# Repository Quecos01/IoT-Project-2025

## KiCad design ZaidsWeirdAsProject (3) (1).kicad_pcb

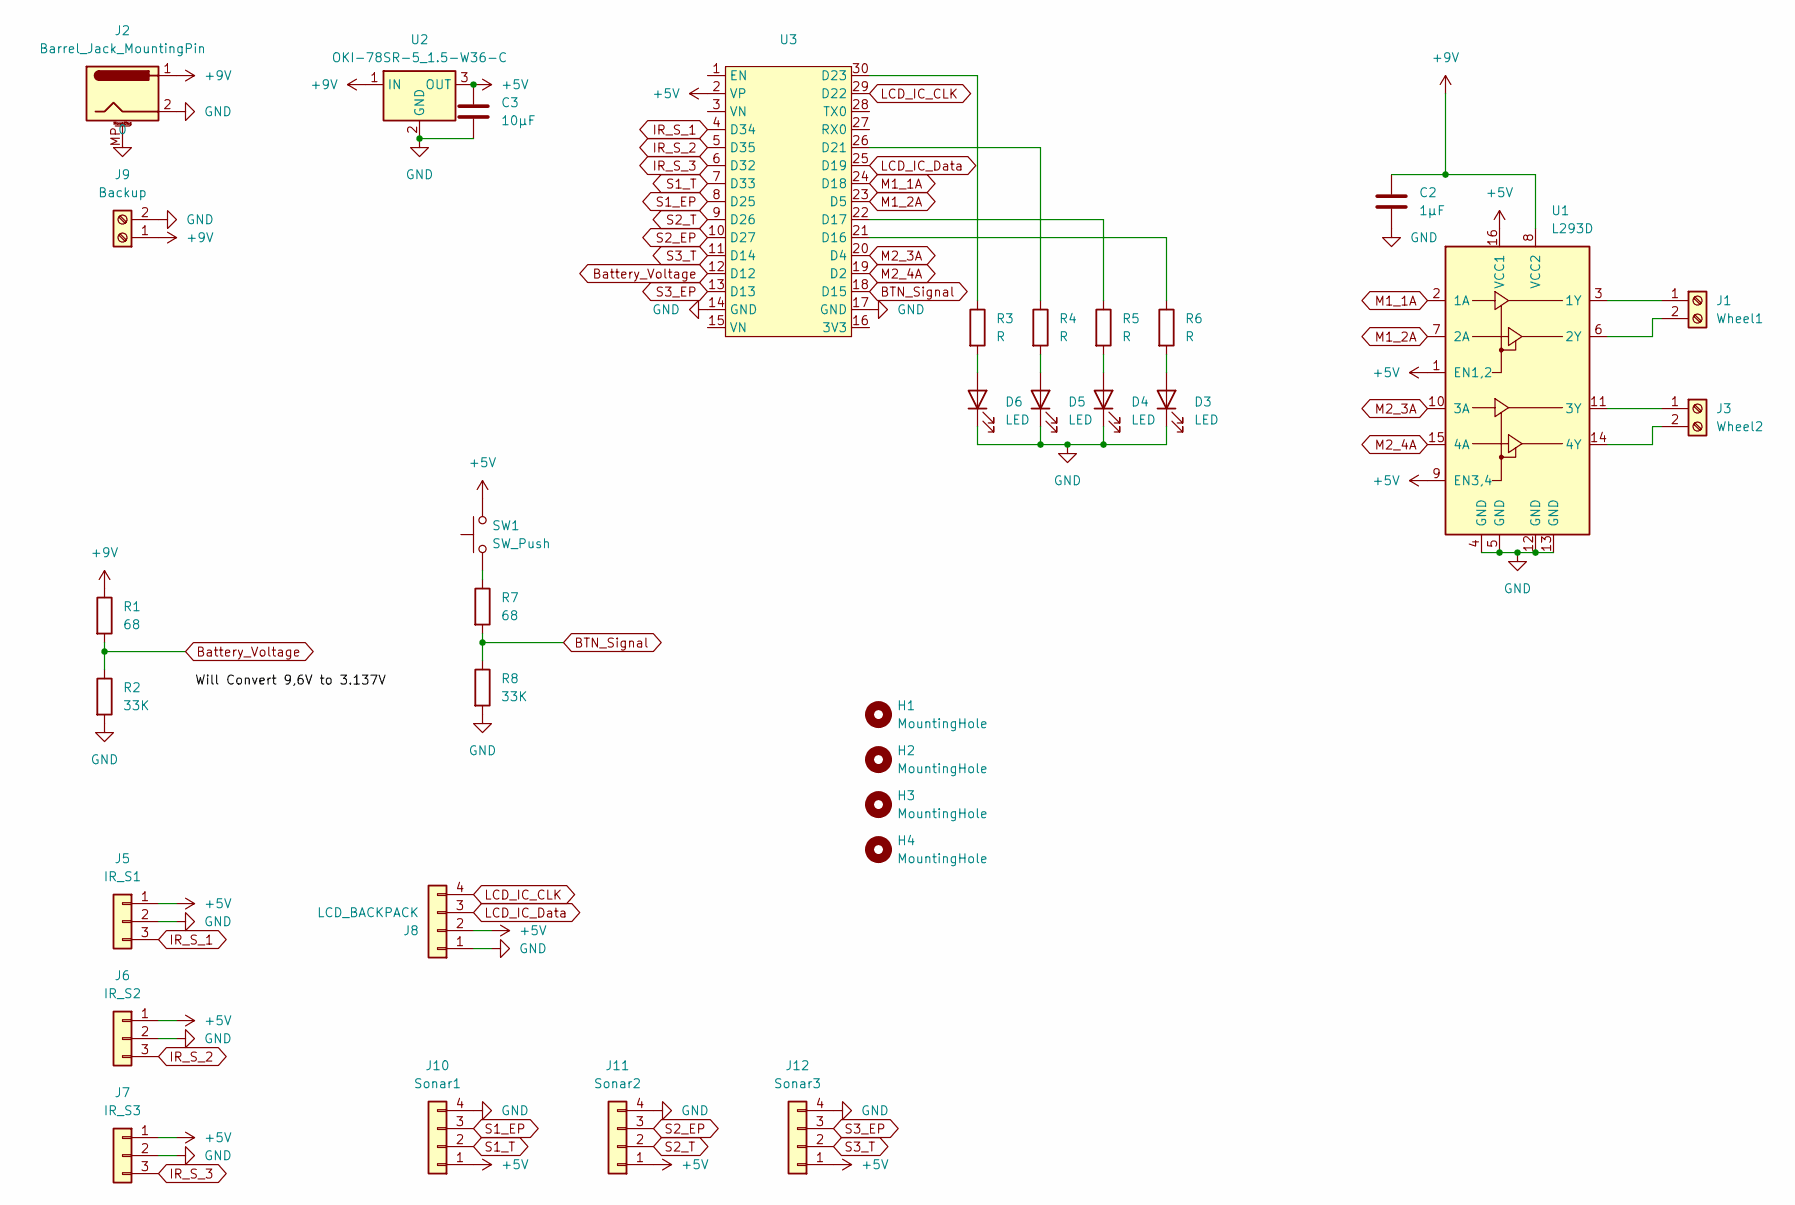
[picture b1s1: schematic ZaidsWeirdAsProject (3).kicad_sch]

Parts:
C2: 1µF; C_Disc_D3.0mm_W1.6mm_P2.50mm
C3: 10µF; C_Disc_D3.0mm_W1.6mm_P2.50mm
D3, D4, D5, D6: LED; LED_D3.0mm
H1, H2, H3, H4: MountingHole; MountingHole_3.2mm_M3
J1: Wheel1; TerminalBlock_Phoenix_MKDS-1,5-2-5.08_1x02_P5.08mm_Horizont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
J2: Barrel_Jack_MountingPin; BarrelJack_CUI_PJ-063AH_Horizontal
J3: Wheel2; TerminalBlock_Phoenix_MKDS-1,5-2-5.08_1x02_P5.08mm_Horizont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
J5: IR_S1; PinHeader_1x03_P2.54mm_Vertical
J6: IR_S2; PinHeader_1x03_P2.54mm_Vertical
J7: IR_S3; PinHeader_1x03_P2.54mm_Vertical
J8: LCD_BACKPACK; PinHeader_1x04_P2.54mm_Vertical
J9: Backup; TerminalBlock_Phoenix_MKDS-1,5-2-5.08_1x02_P5.08mm_Horizont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
J10: Sonar1; PinHeader_1x04_P2.54mm_Vertical
J11: Sonar2; PinHeader_1x04_P2.54mm_Vertical
J12: Sonar3; PinHeader_1x04_P2.54mm_Vertical
R1, R7: 68; R_Axial_DIN0204_L3.6mm_D1.6mm_P7.62mm_Horizontal
R2, R8: 33K; R_Axial_DIN0204_L3.6mm_D1.6mm_P7.62mm_Horizontal
R3, R4, R5, R6: R; R_Axial_DIN0204_L3.6mm_D1.6mm_P7.62mm_Horizontal
SW1: SW_Push; SW_PUSH-12mm
U1: L293D; DIP-16_W7.62mm
U2: OKI-78SR-5_1.5-W36-C; Converter_DCDC_Murata_OKI-78SR_Vertical
U3: ZaidESP32-C3-DevKitM-1

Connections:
0: J2.MP (MountPin)
+5V: C3.1, J5.1, J6.1, J7.1, J8.2, J10.1, J11.1, J12.1, SW1.2, U1.1 (EN1,2), U1.9 (EN3,4), U1.16 (VCC1), U2.3 (OUT), U3.2 (VP)
+9V: C2.1, J2.1, J9.1, R1.1, U1.8 (VCC2), U2.1 (IN)
BTN_Signal: R7.2, R8.1, U3.18 (D15)
Battery_Voltage: R1.2, R2.1, U3.12 (D12)
GND: C2.2, C3.2, D3.1 (K), D4.1 (K), D5.1 (K), D6.1 (K), J2.2, J5.2, J6.2, J7.2, J8.1, J9.2, J10.4, J11.4, J12.4, R2.2, R8.2, U1.4 (GND), U1.5 (GND), U1.12 (GND), U1.13 (GND), U2.2 (GND), U3.14 (GND), U3.17 (GND)
IR_S_1: J5.3, U3.4 (D34)
IR_S_2: J6.3, U3.5 (D35)
IR_S_3: J7.3, U3.6 (D32)
LCD_IC_CLK: J8.4, U3.29 (D22)
LCD_IC_Data: J8.3, U3.25 (D19)
M1_1A: U1.2 (1A), U3.24 (D18)
M1_2A: U1.7 (2A), U3.23 (D5)
M2_3A: U1.10 (3A), U3.20 (D4)
M2_4A: U1.15 (4A), U3.19 (D2)
unnamed: D3.2 (A), R6.2
unnamed: D4.2 (A), R5.2
unnamed: D5.2 (A), R4.2
unnamed: D6.2 (A), R3.2
unnamed: J1.1, U1.3 (1Y)
unnamed: J1.2, U1.6 (2Y)
unnamed: J3.1, U1.11 (3Y)
unnamed: J3.2, U1.14 (4Y)
unnamed: R7.1, SW1.1
unnamed: R6.1, U3.21 (D16)
unnamed: R5.1, U3.22 (D17)
unnamed: R4.1, U3.26 (D21)
unnamed: R3.1, U3.30 (D23)
S1_EP: J10.3, U3.8 (D25)
S1_T: J10.2, U3.7 (D33)
S2_EP: J11.3, U3.10 (D27)
S2_T: J11.2, U3.9 (D26)
S3_EP: J12.3, U3.13 (D13)
S3_T: J12.2, U3.11 (D14)

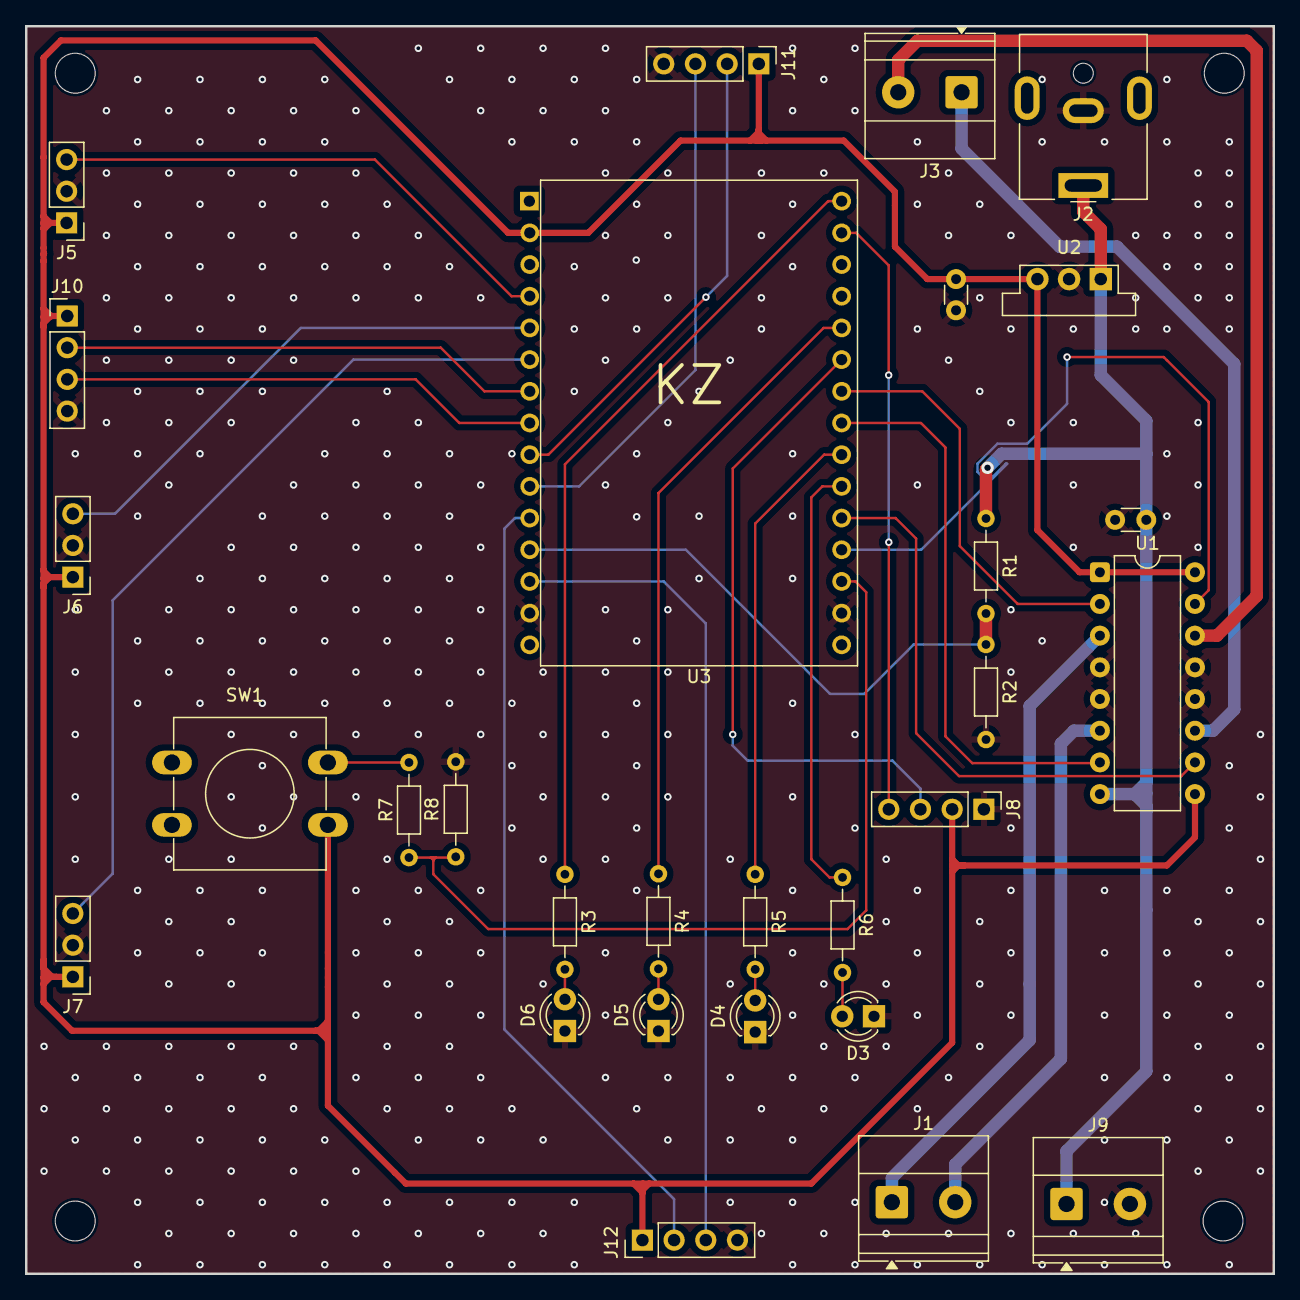
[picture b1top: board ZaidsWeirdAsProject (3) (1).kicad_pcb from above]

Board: 2 copper layers, 100.0 x 100.0 mm, 33 parts (0 on the bottom side), 33 nets.
